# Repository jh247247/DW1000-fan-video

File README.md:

# DW1000 fan pointing thingamagjig

This is the system shown off in [My video](https://youtu.be/dcd7I6KgY1Y) where I make an indoor location system to get a fan to point at me.

This uses the DW1000 UWB module to determine distances between radios in a 3d space, at minimum 4 fixed anchors.

This is very MVP software without power or feature optimizations, but it does work.

# Principle of operation

The DW1000 can determine distances between 2 radios using what is called Asymmetric Two Way Ranging. You can read about it here: https://www.qorvo.com/products/d/da008448

Using those distances, you can uniquely determine a point in 3d space that a radio exists in, given that space has at least 4 stationary radios spread out the area.

Since the measurements in this system are imperfect, the Levenberg-Marquandt algorithm is used to minimize the error in the measurements and find the best fitting point the tag could exist in.

Therefore, by finding the tag's position in 3d space you can have fun interations between them!

The application given in the linked video is trivial, but is an actual in-the-wild application of the technology outside of proof of concepts.
Future work that may or may not be added here:

- a CNC gantry to move a camera to a location given by another tag
- a gimbal for a spotlight to point at a subject
- "Hot zones" where emergency stops are enabled when a subject enters a known dangerous area
- ???

# Structure

Everything here can be considered MVP at best or broken at worst.

_hardware_
This is currently the broken version shown in the video, it has to be patched to get everything working. Hopefully I can get around to it.

- The power supply in power.sch is completely wrong - VCC is taken off the wrong side of the inductor
- MOSI is not attached to the DW1000
- RST is not attached to the DW1000 (optional - can have polling instead)
- IRQ is not attached to the DW1000 (optional - can have polling instead)
- The QMC5883L Compass is not working and doesn't respond to I2C commands - unknown as to why

# Installation

1. Have a home assistant instance up and running with an MQTT server and node-red
2. Add your secrets (WIFI SSID, Password, mqtt server, hopes and dreams) to secrets.cpp
3. Plug in your hardware into usb and run the esp32-s3 target (via platform.io) to run a skeleton sketch that prints out info
4. Note down the host name
5. Modify the platformio.ini file to add a target for your specific hardware. Add either `-DDW1000_ANCHOR` or `-DDW1000_TAG` to set that board as an anchor or tag. Examples from my hardware is provided.
6. Program your board ota using the new platform.io target you've added
7. Rinse and repeat for all your boards.
8. Import the `flows.json` file into your node red instance and duplicate the `Tag` subflow nodes. Add your mac address as it appears in the logs as the `TAG_MAC` env var for that subflow
9. Make sure you add the coordinates for the anchors, this is completely up to you. I recommend setting one as (0,0) with some height off the ground to reference off that one
10. The coordinates for your tags should start updating automatically and be available in Home Assistant for your automations
11. ???
12. Profit!

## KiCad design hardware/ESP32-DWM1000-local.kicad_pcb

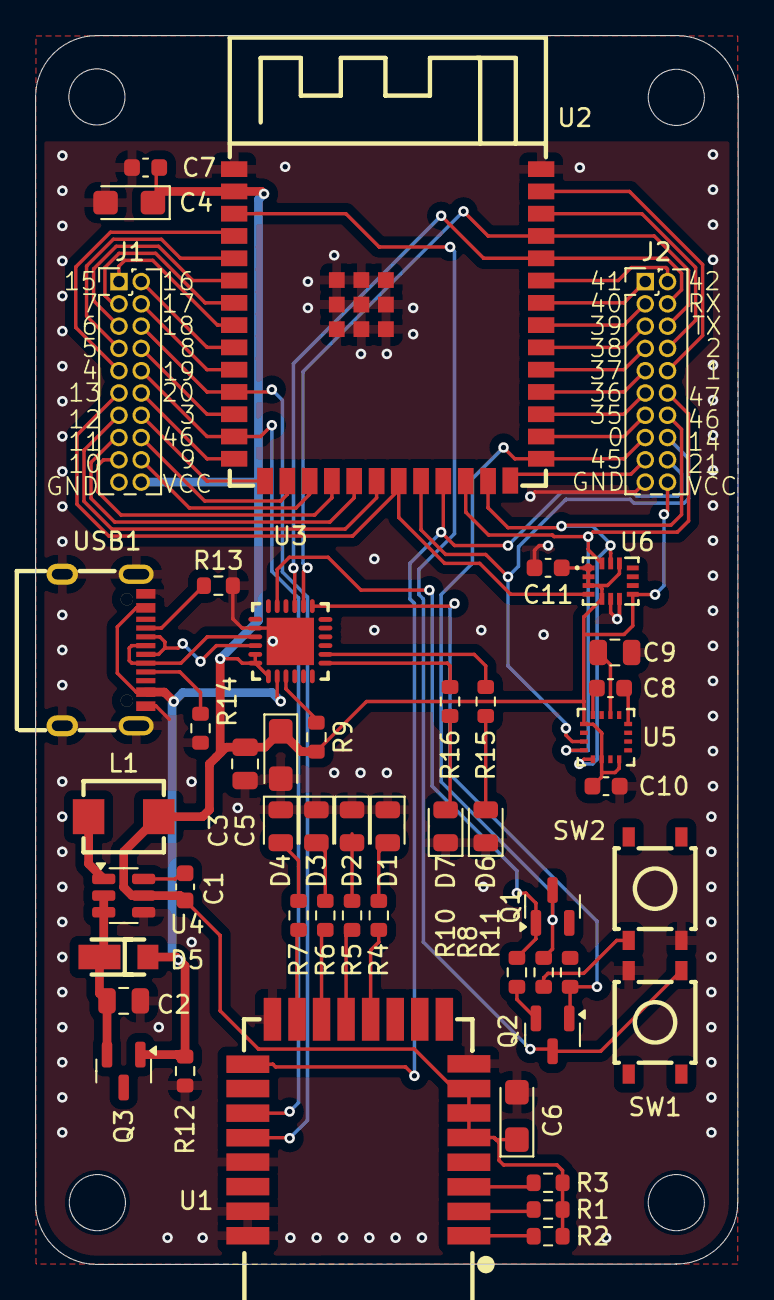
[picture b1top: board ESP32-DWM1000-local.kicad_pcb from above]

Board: 2 copper layers, 40.1 x 70.1 mm, 53 parts (0 on the bottom side), 71 nets.

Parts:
C1, C7, C10, C11: 100n; C_0603_1608Metric
C2, C3: 10u; C_0805_2012Metric
C4, C5, C6: 47u; CP_EIA-3216-10_Kemet-I
C8: 220n; C_0603_1608Metric
C9: 4.7u; C_0805_2012Metric
D1, D2, D3, D4, D6, D7: LED; LED_0805_2012Metric
D5: SBR3M30P1-7; POWERDI123_L2.8-W1.8-LS3.7-RD
H1, H2, H3, H4: MountingHole; MountingHole_3.2mm_M3
J1, J2: Conn_02x10_Odd_Even; PinHeader_2x10_P1.27mm_Vertical
L1: MDA4020-2R2M; IND-SMD_L4.5-W4.1_YXMAA0402
Q1, Q2: S8050; SOT-23
Q3: AO3401A; SOT-23
R1, R2, R3, R4, R5, R6, R7, R8, R10, R11, R15, R16: 470R; R_0603_1608Metric
R9: 4.7k; R_0603_1608Metric
R12: 100k; R_0603_1608Metric
R13, R14: 5.1k; R_0603_1608Metric
SW1, SW2: GT-TC070B-H016-L1; SW-SMD_4P-L4.6-W4.6-P3.00-LS6.1
U1: DWM1000; WIRELM-TH_DWM1000
U2: ESP32-S3-WROOM-1(N16R8); WIRELM-SMD_ESP32-S3-WROOM-1
U3: CP2102N-A02-GQFN24R; QFN-24_L4.0-W4.0-P0.50-TL-EP2.6
U4: AP63203WU; TSOT-23-6
U5: QMC5883L; LGA-16_L3.0-W3.0-P0.50-BL_SQ
U6: LSM6DSLTR; LGA-14_L3.0-W2.5-P0.50-TL
USB1: TYPE-C 16PIN 2MD(073); USB-C-SMD_TYPE-C-6PIN-2MD-073

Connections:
CP2102_DM: U3.4 (D-), USB1.5 (DN2), USB1.7 (DN1)
CP2102_DP: U3.3 (D+), USB1.6 (DP1), USB1.8 (DP2)
CP2102_DTR: Q1.1 (E), R10.2, U3.23 (DTR)
CP2102_REGIN: C1.1, C3.1, C4.1, C5.1, C6.1, C7.1, C10.2, C11.2, J1.20, J2.20, L1.1, R1.1, R2.1, R3.1, R9.1, U1.5 (VDDAON), U1.6 (VDD3V3), U1.7 (VDD3V3), U2.2 (3V3), U3.5 (VIO), U3.6 (VDD), U3.7 (VREGIN), U4.5 (SW), U5.2 (VDD), U5.4 (S1), U5.13 (VDDIO), U6.1 (SDO/SA0), U6.2 (SDX), U6.3 (SCX), U6.5 (VDDIO), U6.8 (VDD), U6.12 (CS)
CP2102_RTS: Q2.1 (E), R11.2, U3.19 (RTS)
CP2102_RX: J2.6, U2.37 (TXD0), U3.20 (RXD)
CP2102_RXLED: R16.2, U3.13 (GPIO.1/RXT)
CP2102_TX: J2.4, U2.36 (RXD0), U3.21 (TXD)
CP2102_TXLED: R15.2, U3.14 (GPIO.0/TXT)
CP2102_VBUS: D5.1 (A), Q3.1 (G), R12.1, U3.8 (VBUS), USB1.2 (VBUS), USB1.11 (VBUS)
DWM_LEDRXOK: R7.2, U1.15 (GPIO0RXOKLED)
DWM_LEDTX: R4.2, U1.12 (GPIO3TXLED)
DWM_RXLED: R5.2, U1.13 (GPIO2RXLED)
DWM_SFDLED: R6.2, U1.14 (GPIO1SFDLED)
GND: C2.2, C3.2, C4.2, C5.2, C6.2, C7.2, C9.2, C10.1, C11.1, D1.1 (K), D2.1 (K), D3.1 (K), D4.1 (K), D6.1 (K), D7.1 (K), J1.19, J2.19, R12.2, R13.2, R14.2, SW1.3, SW2.3, U1.8 (VSS), U1.16 (VSS), U1.21 (VSS), U1.23 (VSS), U1.24 (VSS), U2.1 (GND), U2.40 (GND), U2.41 (GND), U3.2 (GND), U3.25 (GND), U4.4 (GND), U5.9 (GND), U5.11 (GND), U6.6 (GND), U6.7 (GND), USB1.1 (GND), USB1.12 (GND), USB1.13 (SHELL), USB1.14 (SHELL)
I2C_SCL: J2.14, U2.25 (IO48), U5.1 (SCL), U6.13 (SCL)
I2C_SDA: J2.12, U2.24 (IO47), U5.16 (SDA), U6.14 (SDA)
IO0: J2.15, Q1.3 (C), R8.1, U2.27 (IO0)
IO1: J2.10, U2.39 (IO1)
IO2: J2.8, U2.38 (IO2)
IO3: J1.14, U2.15 (IO3)
IO4: J1.9, U2.4 (IO4)
IO5: J1.7, U2.5 (IO5)
IO6: J1.5, U2.6 (IO6)
IO7: J1.3, U2.7 (IO7)
IO8: J1.8, U2.12 (IO8)
IO9: J1.18, U2.17 (IO9)
IO10: J1.17, U2.18 (IO10)
IO11: J1.15, U2.19 (IO11)
IO12: J1.13, U2.20 (IO12)
IO13: J1.11, U2.21 (IO13), U6.4 (INT1)
IO14: J2.16, U2.22 (IO14), U5.15 (DRDY)
IO15: J1.1, U2.8 (IO15)
IO16: J1.2, U2.9 (IO16)
IO17: J1.4, U2.10 (IO17)
IO18: J1.6, U1.20 (SPICLK), U2.11 (IO18)
IO19: J1.10, U1.19 (SPIMISO), U2.13 (IO19)
IO20: J1.12, U2.14 (IO20)
IO21: J2.18, U1.17 (SPICSn), U2.23 (IO21)
IO35: J2.13, U2.28 (IO35)
IO36: J2.11, U2.29 (IO36)
IO37: J2.9, U2.30 (IO37)
IO38: J2.7, U2.31 (IO38)
IO39: J2.5, U2.32 (IO39)
IO40: J2.3, U2.33 (IO40)
IO41: J2.1, U2.34 (IO41)
IO42: J2.2, U2.35 (IO42)
IO45: J2.17, U2.26 (IO45)
IO46: J1.16, U2.16 (IO46)
unnamed: D1.2 (A), R4.1
unnamed: D2.2 (A), R5.1
unnamed: D3.2 (A), R6.1
unnamed: D4.2 (A), R7.1
unnamed: C2.1, D5.2 (K), Q3.2 (S), U4.2 (EN), U4.3 (IN)
unnamed: D6.2 (A), R15.1
unnamed: D7.2 (A), R16.1
unnamed: Q1.2 (B), R11.1
unnamed: Q2.2 (B), R10.1
unnamed: R8.2, SW2.1
unnamed: R2.2, U1.1 (EXTON)
unnamed: R3.2, U1.3 (RSTn)
unnamed: R1.2, U1.2 (WAKEUP)
unnamed: R9.2, U3.9 (RSTb)
unnamed: C1.2, U4.6 (BST)
unnamed: L1.2, U4.1 (FB)
unnamed: C9.1, U5.10 (C1)
unnamed: C8.2, U5.12 (SETC)
unnamed: C8.1, U5.8 (SETP)
unnamed: R13.1, USB1.4 (CC1)
unnamed: R14.1, USB1.9 (SBU1)
RESET: Q2.3 (C), SW1.1, U2.3 (EN)

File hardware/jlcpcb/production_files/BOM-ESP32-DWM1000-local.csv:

Comment,Designator,Footprint,LCSC,Quantity
470R,"R1,R10,R11,R15,R16,R2,R3,R4,R5,R6,R7,R8",R_0603_1608Metric,C114669,12
LSM6DSLTR,U6,LGA-14_L3.0-W2.5-P0.50-TL,C126672,1
AO3401A,Q3,SOT-23,C15127,1
100n,"C1,C10,C11,C7",C_0603_1608Metric,C1525,4
47u,"C4,C5,C6",CP_EIA-3216-10_Kemet-I,C16780,3
10u,"C2,C3",C_0805_2012Metric,C17024,2
S8050,"Q1,Q2",SOT-23,C181158,2
220n,C8,C_0603_1608Metric,C21120,1
4.7k,R9,R_0603_1608Metric,C23162,1
5.1k,"R13,R14",R_0603_1608Metric,C23186,2
100k,R12,R_0603_1608Metric,C25803,1
TYPE-C 16PIN 2MD(073),USB1,USB-C-SMD_TYPE-C-6PIN-2MD-073,C2765186,1
GT-TC070B-H016-L1,"SW1,SW2",SW-SMD_4P-L4.6-W4.6-P3.00-LS6.1,C2843954,2
MDA4020-2R2M,L1,IND-SMD_L4.5-W4.1_YXMAA0402,C2847469,1
ESP32-S3-WROOM-1(N16R8),U2,WIRELM-SMD_ESP32-S3-WROOM-1,C2913202,1
SBR3M30P1-7,D5,POWERDI123_L2.8-W1.8-LS3.7-RD,C460953,1
Conn_02x10_Odd_Even,"J1,J2",PinHeader_2x10_P1.27mm_Vertical,C7470093,2
AP63203WU,U4,TSOT-23-6,C780769,1
DWM1000,U1,WIRELM-TH_DWM1000,C95238,1
LED,"D1,D2,D3,D4,D6,D7",LED_0805_2012Metric,C965813,6
CP2102N-A02-GQFN24R,U3,QFN-24_L4.0-W4.0-P0.50-TL-EP2.6,C969151,1
QMC5883L,U5,LGA-16_L3.0-W3.0-P0.50-BL_SQ,C976032,1
4.7u,C9,C_0805_2012Metric,C98192,1

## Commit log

2025-02-05 Actually add content to readme
